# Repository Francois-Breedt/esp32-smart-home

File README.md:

# ESP32 Smart Home

A modular smart-home hardware and firmware project built around the **ESP32-C3 Super Mini**. The first module combines room-presence detection, ambient-light measurement, and addressable LED control. A Raspberry Pi is intended to provide central coordination.

> **Project status:** Initial repository scaffold. Hardware choices below reflect the current design notes; some implementation details still need confirmation and testing.

## Current design

- **Controller:** ESP32-C3 Super Mini, powered through its 5 V pin
- **Presence:** HLK-LD2410C radar module, using its digital `OUT` output
- **Optional expansion:** second presence-sensor input
- **Ambient light:** BH1750 I²C illuminance sensor
- **Lighting:** addressable LED strip, driven through a 5 V logic-level shifter
- **Power:** Mean Well 5 V / 6 A / 30 W supply
- **PCB:** custom board with bulk capacitance, local ESP32/level-shifter decoupling, series LED-data resistor, and extra LED power/sensor terminals
- **Enclosure:** planned 3D-printed enclosure
- **Central system:** Raspberry Pi
- **Audio:** intentionally outside the scope of this ESP32-C3 module

## Repository layout

```text
docs/                 Wiring, pinout, power, assembly, and troubleshooting
firmware/esp32-c3/    Starter firmware project (PlatformIO / Arduino framework)
hardware/             PCB, schematic, and bill-of-materials placeholders
raspberry-pi/         Notes for central coordination and integration
images/               Project photos and diagrams
```

## Pin assignment

| Function | ESP32-C3 GPIO | Notes |
|---|---:|---|
| BH1750 SDA | GPIO0 | I²C data |
| BH1750 SCL | GPIO1 | I²C clock |
| Presence sensor 1 OUT | GPIO3 | Digital input |
| Presence sensor 2 OUT | GPIO4 | Optional digital input |
| LED data | GPIO10 | Connect to the level-shifter input |

Verify the exact pin labels on the specific ESP32-C3 Super Mini board revision before wiring. Keep boot-strapping and board-specific pin behaviour in mind when changing the pinout.

## Getting started

1. Read [`docs/hardware-overview.md`](docs/hardware-overview.md) and [`docs/wiring.md`](docs/wiring.md).
2. Install [PlatformIO](https://platformio.org/) in VS Code, or use the PlatformIO CLI.
3. Open `firmware/esp32-c3/` as the PlatformIO project.
4. Build and upload the starter firmware.
5. Open the serial monitor at **115200 baud** to see sensor readings.
6. Confirm sensor polarity and LED-strip type before enabling any lighting automation.

The starter firmware is deliberately conservative: it reports sensor state and illuminance, and provides a basic configurable LED test/response. It is not yet a complete home-automation integration.

## Important electrical notes

- The 5 V / 6 A supply can deliver substantial current. Size wiring, connectors, copper, and protection for the expected load.
- Do **not** route LED-strip current through the ESP32 board.
- Connect the LED strip's power directly to the appropriate 5 V/GND distribution, and connect grounds together so the data signal has a reference.
- Confirm that the level shifter is suitable for the LED protocol and that its supply and enable pins are wired correctly.
- Mains wiring is hazardous. Enclose and strain-relieve it properly, maintain separation between mains and low-voltage circuits, and have the mains side assembled/checked by a qualified person.
- The exact LED model, strip length, current draw, connector ratings, fuse strategy, and final PCB layout must be verified before installation.

## Documentation

- [Hardware overview](docs/hardware-overview.md)
- [Pinout](docs/pinout.md)
- [Wiring](docs/wiring.md)
- [Power supply](docs/power-supply.md)
- [PCB design notes](docs/pcb-design.md)
- [Assembly](docs/assembly.md)
- [Firmware configuration](docs/configuration.md)
- [Troubleshooting](docs/troubleshooting.md)
- [Raspberry Pi integration](raspberry-pi/README.md)

## Contributing / revisions

Track hardware changes with PCB revision identifiers and update the wiring/pinout documents whenever a connector, component, or GPIO assignment changes. Avoid committing Wi-Fi passwords, API tokens, private network credentials, or other secrets.

## License

This repository currently uses the MIT License; see [`LICENSE`](LICENSE). Change it before publishing if you prefer another license.

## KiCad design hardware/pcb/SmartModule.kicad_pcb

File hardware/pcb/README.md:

# PCB design

Place the editable PCB project and revision-specific exports here.

Recommended exports:
- PCB source file(s)
- Gerbers and drill files
- Pick-and-place / CPL file, if applicable
- Assembly drawing
- PCB render or screenshot
- Revision notes

Add the actual design files yourself when ready.

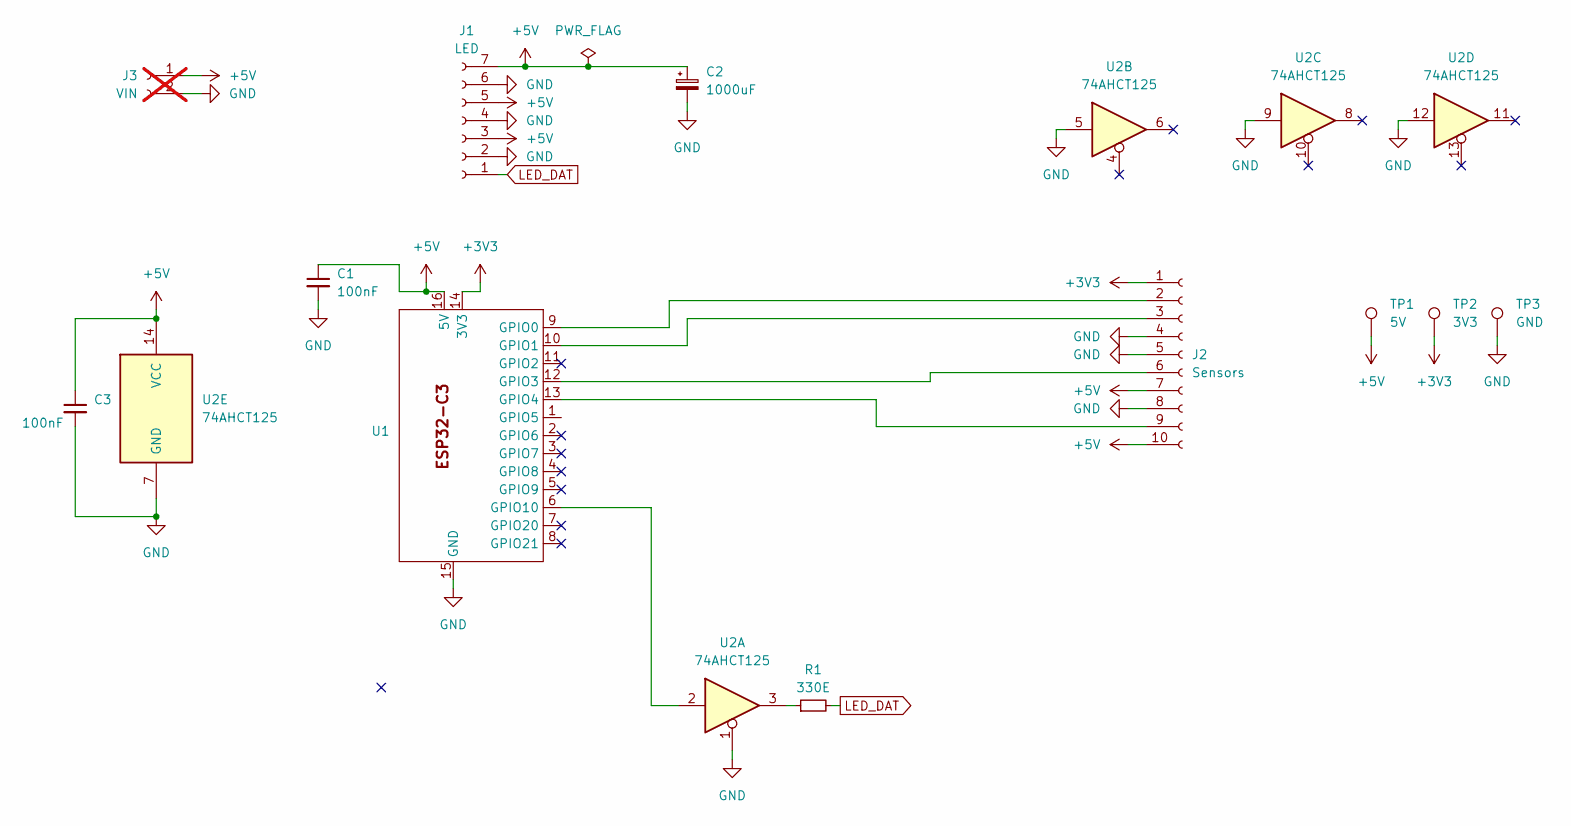
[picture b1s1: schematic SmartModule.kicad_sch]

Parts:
C1, C3: 100nF; C_Disc_D5.0mm_W2.5mm_P5.00mm
C2: 1000uF; CP_Radial_D6.3mm_P2.50mm
J1: LED; TerminalBlock_TE_282834-7_1x07_P2.54mm_Horizontal
J2: Sensors; TerminalBlock_Phoenix_MPT-0,5-10-2.54_1x10_P2.54mm_Horizont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
J3: VIN; TerminalBlock_Phoenix_MPT-0,5-2-2.54_1x02_P2.54mm_Horizontal; not fitted
R1: 330E; R_Axial_DIN0204_L3.6mm_D1.6mm_P5.08mm_Horizontal
TP1: 5V; TestPoint_Pad_3.0x3.0mm
TP2: 3V3; TestPoint_Pad_3.0x3.0mm
TP3: GND; TestPoint_Pad_3.0x3.0mm
U1: ESP32-C3 Supermini
U2: 74AHCT125; SOIC-14_3.9x8.7mm_P1.27mm

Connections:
+3V3: J2.1, TP2.1, U1.14 (3V3)
+5V: C1.1, C2.1, C3.1, J1.3, J1.5, J1.7, J2.7, J2.10, J3.1, TP1.1, U1.16 (5V), U2.14 (VCC)
GND: C1.2, C2.2, C3.2, J1.2, J1.4, J1.6, J2.4, J2.5, J2.8, J3.2, TP3.1, U1.15 (GND), U2.1, U2.5, U2.7 (GND), U2.9, U2.12
LED_DAT: J1.1, R1.2
unnamed: J2.2, U1.9 (GPIO0)
unnamed: J2.3, U1.10 (GPIO1)
unnamed: J2.6, U1.12 (GPIO3)
unnamed: J2.9, U1.13 (GPIO4)
unnamed: R1.1, U2.3
unnamed: U1.6 (GPIO10), U2.2

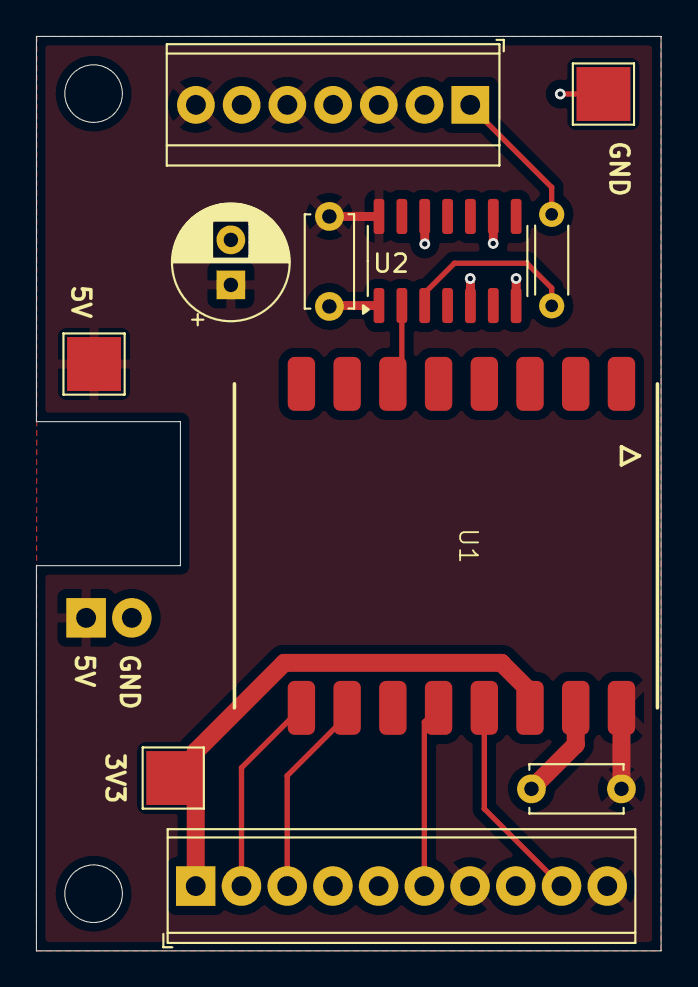
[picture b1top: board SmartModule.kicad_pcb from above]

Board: 2 copper layers, 34.7 x 50.8 mm, 12 parts (0 on the bottom side), 10 nets.
